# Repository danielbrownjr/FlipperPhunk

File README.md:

# FlipperPhunk — RS-232 Bridge/Logger/MitM for Flipper Zero

An inline RS232 interception rig for authorized security testing: a small
level-shifter board sits between two serial devices, and a Flipper Zero app
relays, logs, and can inject on the wire in real time.

> **Authorized use only.** This is a dual-use security tool intended for
> engagements you are authorized to test (pentests, red-team work, your own
> lab equipment) or CTF/research use. Intercepting communications you do not
> own or have written authorization to test is illegal in most jurisdictions
> (e.g. wiretapping statutes, CFAA-adjacent laws). Keep engagement paperwork
> on hand when using this in the field.

## How it works

Rev C.1 uses one Adafruit 5987 RS232 Pal module as the dual-channel voltage
boundary. J2 is the female HOST/PC connector and uses Flipper USART on GPIO
pins 13/14. J3 is the male INSTRUMENT/DCE connector and uses LPUART on GPIO
pins 15/16. See [`hardware/README.md`](hardware/README.md) for the audited
pin-level mapping.

The board is **inline**, not a passive tap: Device A's TX line is broken and
terminates at the Flipper (via level shifting), and the Flipper's own TX line
feeds Device B's RX — and vice versa. That means the Flipper app is the thing
actually relaying bytes between A and B, so it sees, logs, and can hold or
inject on every byte in both directions. If the Flipper app isn't running or
the relay is paused, the link between A and B is down — there is no
passive fallback path.

Rev C.1 also has no selectable DTE/DCE/null-modem matrix, galvanic isolation,
or implemented fail-safe bypass. Its handshake lines pass straight through
and are not captured by the Flipper.

## Project authority

- **Mem** — current project truth, revision state, and design decisions live
  in a private project-knowledge note (not linked here since this repo is
  public; ask the project owner for access).
- **GitHub** — source code and repository history.
- **Google Drive** — audited schematics, netlists/BOMs, datasheets, and other
  binary/design artifacts live in a private artifact vault (access-controlled
  separately from this repo; ask the project owner for access).

## Repo layout

- `hardware/` — level-shifter board design: schematic description, BOM,
  wiring table from RS232 through to the Flipper GPIO header.
- `firmware/` — the Flipper Zero application (FAP) source.
- `tools/sprite_assets/` — reproducible source-to-Flipper conversion
  pipeline for the firmware's splash-screen mascot animation. See
  `tools/sprite_assets/README.md`.

## Quick start

1. Build the hardware from `hardware/README.md`.
2. Build and deploy the app — see `firmware/README.md`.
3. Connect the host/PC to J2 and the DCE instrument to J3, plug the
   board's ribbon/header into the Flipper's GPIO pins per the wiring table,
   power the board from the Flipper's 3V3 rail (pin 9), launch the app,
   select the baud rate/framing to match the link under test, and start the
   relay.

## Status / limitations

- Firmware targets the stock Flipper Zero firmware `furi_hal_serial` API
  (USART + LPUART channels). It has not yet been flashed to real hardware —
  see `firmware/README.md` for what's been validated (compiles
  under `ufbt`) versus what still needs a bench test.
- Injection is currently a minimal hook (a fixed byte sequence bound to a
  button) rather than a full text-entry UI — documented in the firmware
  README as the natural next extension.
- Both sides currently must run the same baud rate/framing (no rate
  conversion between A and B).
- Hardware behavior remains bench-unverified; do not treat a successful
  firmware build as validation of the complete Rev C.1 assembly.

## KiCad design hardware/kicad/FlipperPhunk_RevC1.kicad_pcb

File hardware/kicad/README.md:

# FlipperPhunk Rev C.1 KiCad project

This directory contains the initial manufacturable-layout capture of Rev C.1.
The design is an active dual-UART bridge/logger; it has no fail-safe bypass,
role switching, isolation, handshake monitoring, or speculative protection
circuitry.

## Open the project

Open `FlipperPhunk_RevC1.kicad_pro` with KiCad 10.0 or later. The project uses
only the project-local `FlipperPhunk.kicad_sym` and `FlipperPhunk.pretty`
libraries.

The generated board is 110.00 x 60.00 mm, two-layer, with four 3.2 mm M3
mounting holes. J2 is on the left edge, J3 is on the right edge, J1 is along
the top edge, and A1 is centered. The reserved `Dwgs.User` rectangles near the
DE-9 connectors intentionally leave space for a possible protection revision.

## Decorative bottom silkscreen

`LOGO1` is a board-only `FlipperPhunk:FlipperPhunk_Mascot_BSilkscreen`
footprint on `B.SilkS`, centered at board coordinate (53.0, 52.5) mm. Its
printed geometry is approximately 24.26 x 22.03 mm inside a 26.00 x 22.67 mm
SVG canvas. It sits in the open region between J2 and A1 and does not overlap
pads, holes, soldermask openings, connector labels, reference designators, or
pin-1/orientation markings.

The exact source is
`../artwork/FlipperPhunk_PCB_Silkscreen_Mascot_Concept.png`, retrieved from
Google Drive file `10mS8YFlCxH06XEhFGrP6FUxIgZma-iS4` (SHA-256
`339200fbbcba0f4e5484f77f06e7da99637f57516e74fdee5ba13d2bedb0f569`). The
source PNG remains unchanged and is not treated as fabrication geometry. The
committed `FlipperPhunk_PCB_Silkscreen_Mascot_Simplified.svg` and KiCad
footprint are monochrome derivatives. Conversion thresholds the source alpha,
uses a 0.25 mm morphological close/open operation, removes isolated regions
below 0.06 mm2, and simplifies vector contours to 0.05 mm. This retains the
recognizable silhouette and pose while removing anti-aliasing, hairlines, and
sub-process details.

The 0.25 mm artwork feature target is deliberately more conservative than
PCBWay's published 0.15 mm minimum legend width. KiCad DRC is clean with the
artwork in place. A fabrication preview should still be reviewed because final
silkscreen clipping and rendering are controlled by the selected board house's
CAM process.

## Exact footprints

- J2: `FlipperPhunk:Wurth_618009231121`, female, right-angle, with hex screws.
- J3: `FlipperPhunk:Wurth_618009231221`, male, right-angle, with hex screws.
- J1: `FlipperPhunk:Samtec_SSW-108-01-F-D`, 2x8, 2.54 mm pitch.
- A1: `FlipperPhunk:Adafruit_5987_Socketed`, implemented by two Samtec
  `SSW-106-01-G-S` 1x6 sockets.

The two Würth footprints reproduce the signal-pad, hex-screw/shell-pad, body,
and courtyard coordinates in Würth's official `KiCad_WR-DSUB (rev26b)` library
and current part drawings. The board placement follows the footprint's PCB-edge
indicator. Pin 1 is square and separately marked. J2 and J3 are deliberately
oriented so the board-side pad numbering agrees with their manufacturer
footprints; the schematic uses the corrected DCE mapping (`J3.2` instrument TX,
`J3.3` instrument RX). Do not infer pin numbering by looking only at the rear of
an unmated connector: verify continuity from each mating-face pin on the first
assembled board.

The Würth `S1` and `S2` hex-screw/shell pads are plated mechanical pads because
the actual parts require them. Both are explicit no-connects in the schematic
and have no PCB net, so the DE-9 shells remain electrically floating.

The A1 footprint uses the verified 17.78 x 20.32 mm rounded module outline,
12.70 mm row spacing, 2.54 mm pin pitch, 1.00 mm socket holes, and a 0.50 mm
assembly courtyard. Its two 2.70 mm carrier holes align with the module's
2.50 mm mounting holes for optional M2.5 standoffs. `V+` and `V-` are explicit
no-connects. The module outline/courtyard is the keep-clear region for tall
parts and exposed carrier pads.

## Routing and electrical decisions

All six handshake signals (pins 1, 4, 6, 7, 8, and 9) are routed as plain
copper from J2 to the same-numbered J3 pin. There are no 0-ohm links. The board
uses a solid B.Cu GND pour and 0.30 mm signal routing. All sixteen canonical
nets are fully connected. There is no TVS/ESD network in Rev C.1.

## Validation

Generated and checked with KiCad 10.0.6:

```powershell
kicad-cli sch erc FlipperPhunk_RevC1.kicad_sch --output erc.rpt
kicad-cli pcb drc FlipperPhunk_RevC1.kicad_pcb --output drc.rpt
```

Current result: ERC 0 errors / 0 warnings; DRC 0 violations / 0 unconnected
items / 0 footprint errors. The board generator requires KiCad's bundled Python
plus `kiutils` 1.4.8 and deterministically rebuilds the electrical footprints,
placement, routing, ground zone, schematic, and placement of the committed
mascot footprint. Rebuilding the mascot derivatives themselves additionally
requires Pillow, NumPy, and `opencv-python-headless`; run
`../artwork/vectorize_mascot.py` first if the source art changes.

The `erc.rpt` and `drc.rpt` files are reproducible local outputs and are
intentionally ignored rather than committed as canonical review evidence. Run
the commands above against the committed design, and record the tool version
and result in the relevant pull request or release notes.

## Mechanical assumptions to resolve before fabrication

No fabrication files are supplied or authorized by this revision. Before any
future order, physically measure or fit-check:

- the exact J2/J3 PCB-edge overhang, mating-face pin numbering, hex-screw
  hardware, and enclosure/panel clearance;
- J1 pin-1 orientation against the actual Flipper GPIO header, plus Flipper
  body/bumper clearance and the `SSW-108-01-F-D` mating height;
- both `SSW-106-01-G-S` socket tail fit, A1 insertion depth, total stack height,
  component-side clearance, and optional M2.5 standoff length;
- the actual Adafruit 5987 mounting-hole diameter/tolerance and whether the
  2.70 mm carrier holes provide the desired fit;
- cable strain and access to all four carrier mounting holes in the intended
  enclosure.

Also perform continuity checks from the DE-9 mating faces to the named nets,
confirm both floating shells, and bench-test on a known-good DTE/DCE link before
considering a fabrication release.

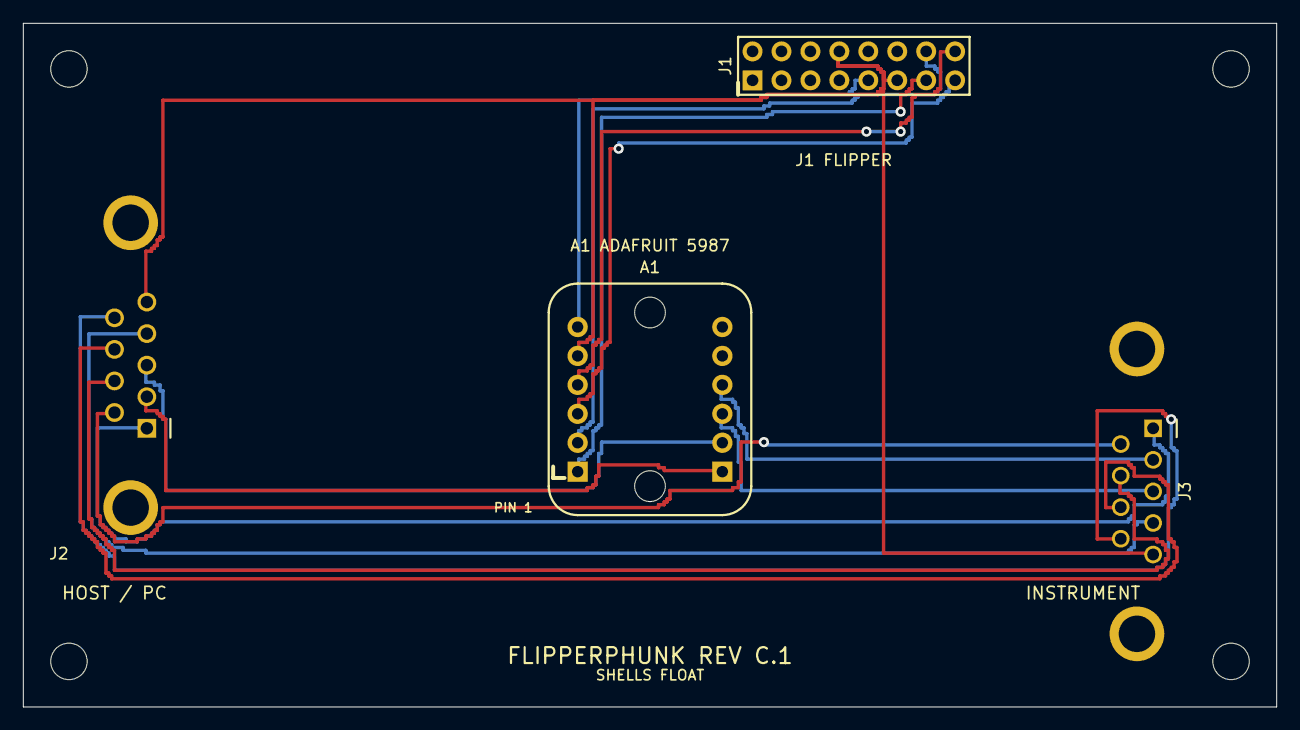
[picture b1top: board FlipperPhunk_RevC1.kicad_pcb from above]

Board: 2 copper layers, 110.0 x 60.0 mm, 9 parts (0 on the bottom side), 16 nets.

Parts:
A1: Adafruit 5987 on 2x Samtec SSW-106-01-G-S; Adafruit_5987_Socketed
H1, H2, H3, H4: M3 mounting hole; MountingHole_3.2mm_M3
J1: Samtec SSW-108-01-F-D; Samtec_SSW-108-01-F-D
J2: Wurth 618009231121; Wurth_618009231121
J3: Wurth 618009231221; Wurth_618009231221
LOGO1: FlipperPhunk mascot - simplified bottom silkscreen; FlipperPhunk_Mascot_BSilkscreen

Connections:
+3V3: A1.6, J1.9
CTS_PASS: J2.8, J3.8
DCD_PASS: J2.1, J3.1
DSR_PASS: J2.6, J3.6
DTR_PASS: J2.4, J3.4
GND: A1.5, J1.8, J1.11, J2.5, J3.5
HOST_RXD: A1.7, J2.2
HOST_TXD: A1.8, J2.3
INST_RXD_FROM_DCE: A1.10, J3.2
INST_TXD_TO_DCE: A1.9, J3.3
LPUART_RX: A1.4, J1.16
LPUART_TX: A1.3, J1.15
RI_PASS: J2.9, J3.9
RTS_PASS: J2.7, J3.7
USART_RX: A1.2, J1.14
USART_TX: A1.1, J1.13
